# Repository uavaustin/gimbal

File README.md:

# gimbal
Hardware and software for UAV Austin's homebrew gimbal.

Notes:
 - MPU two jst connectors align with 7 pin header connected to STM
   - SPI connections
 - Voltage Rgulator rated for 12-13V input. Outputs 3.3V up to 250 mA
 - CP2102 USB to UART converter
 - Boot0 and Boot1 in 3 and 4 pin arrangement for programming settings
   - Boot0 connects to either ground or PWR (3.3V)
   - Boot1  (PB2) connects to ground, PWR, or the motor controller
 - MPU goes on its own board seperate from the STM, DRV, CP2102, USB, and Voltage Regulator
 - Jumper to connect NRST to ground or external input voltage
 - PA13/14 jtag | PB4/5/6/7 SPI on STM
 - 2 sets of 2 header pins to get power from battery

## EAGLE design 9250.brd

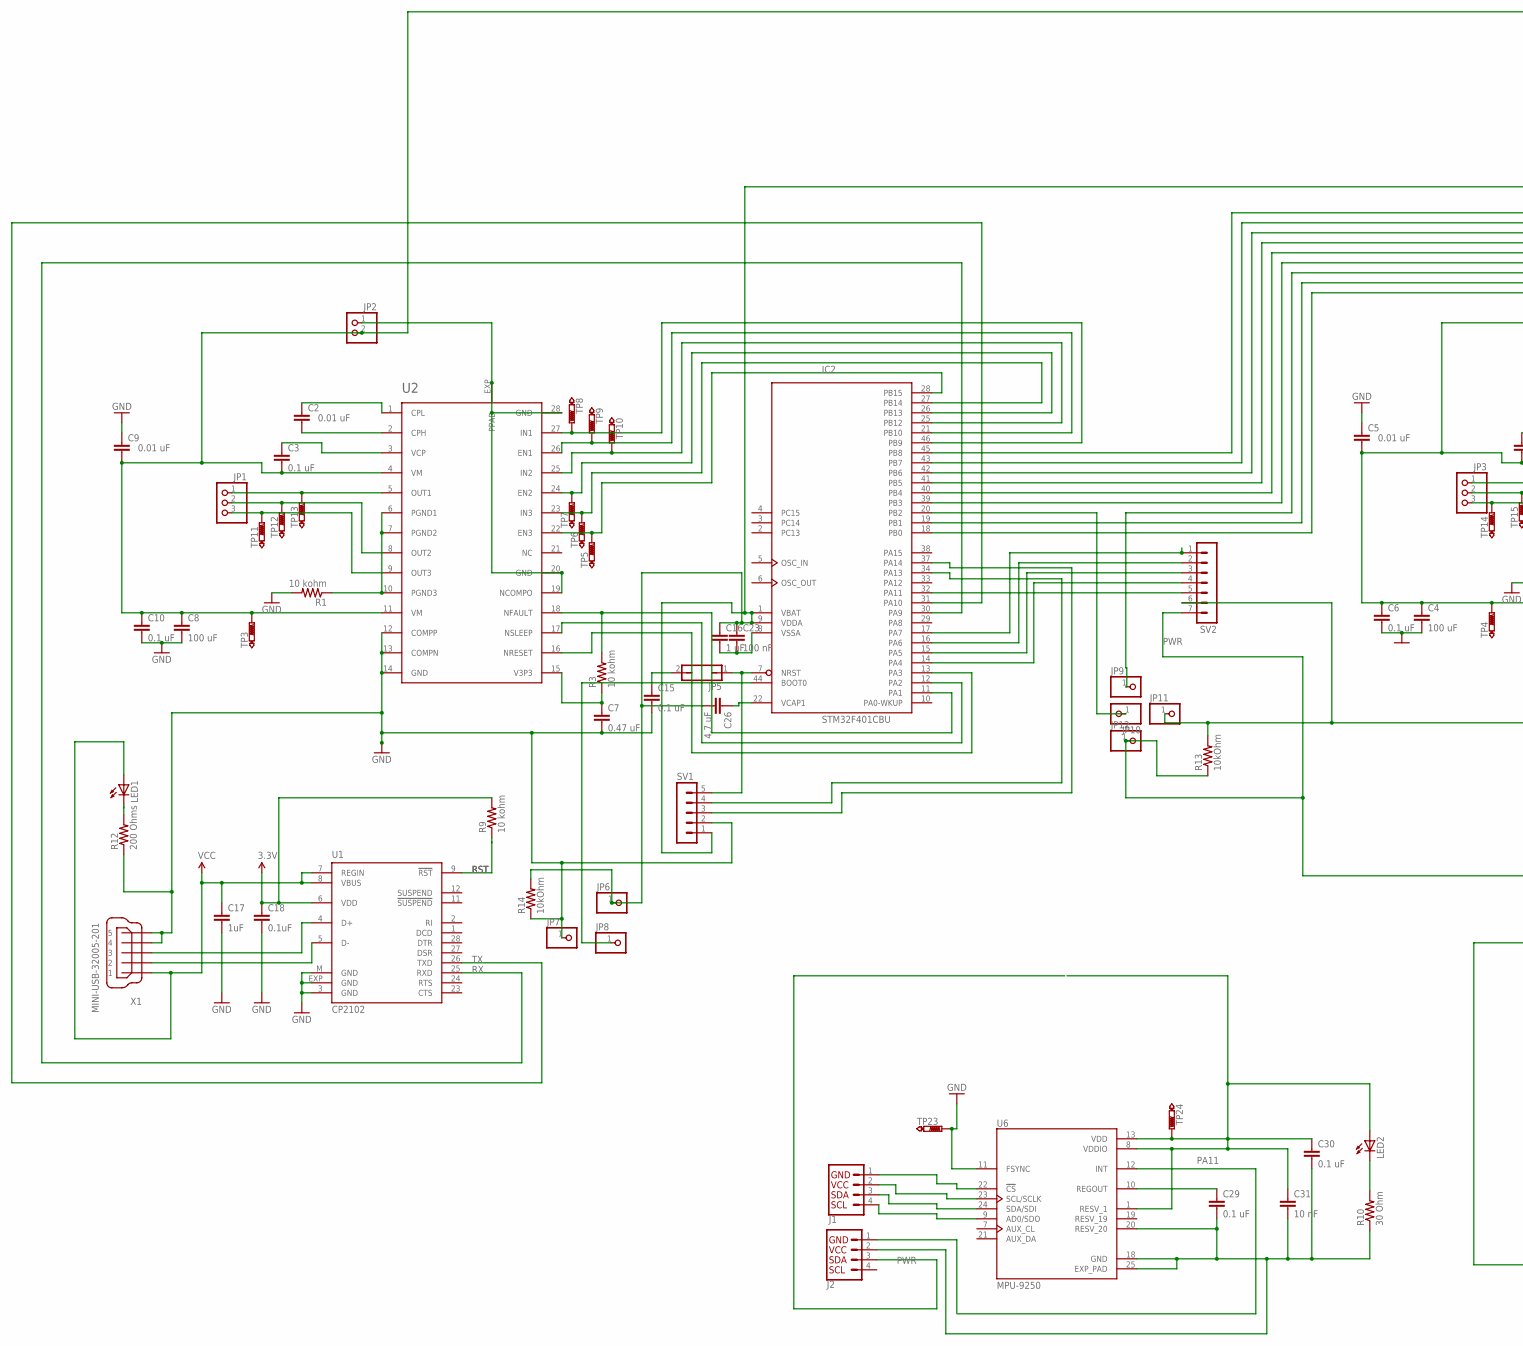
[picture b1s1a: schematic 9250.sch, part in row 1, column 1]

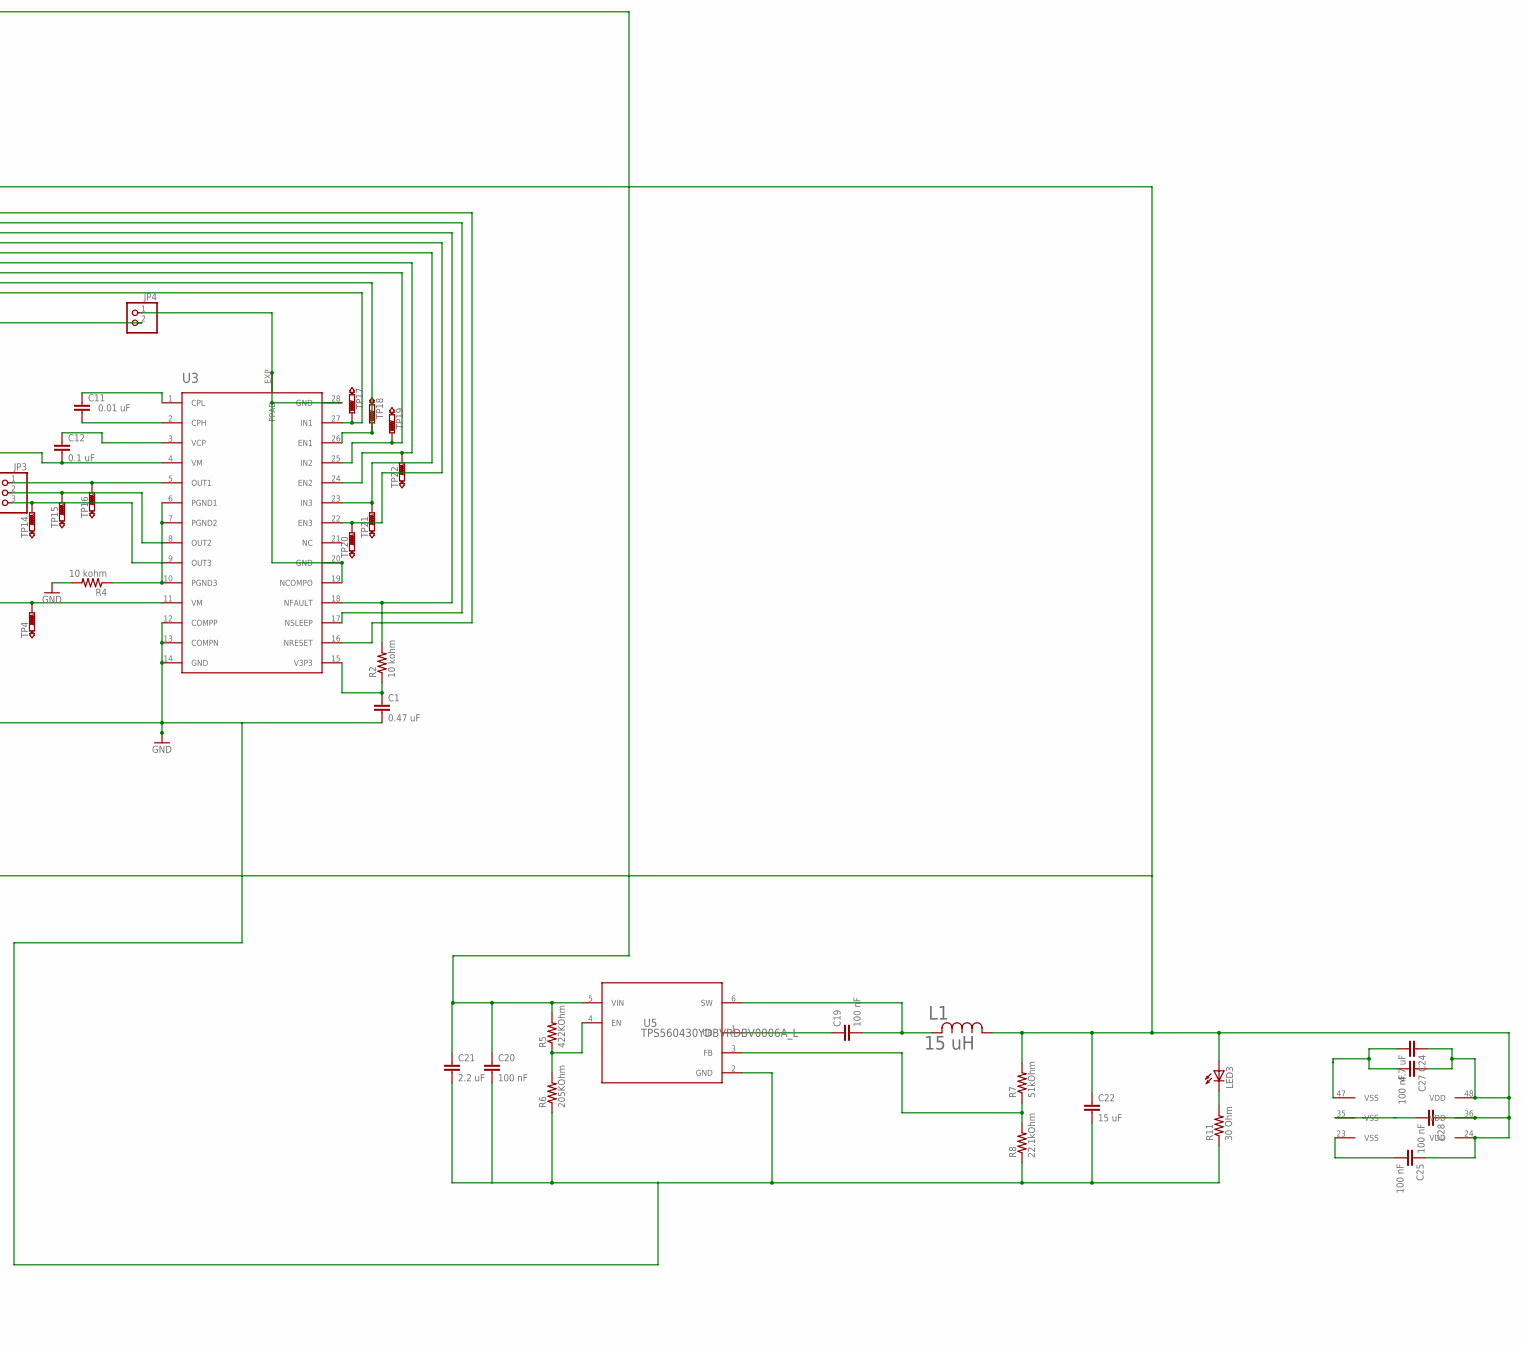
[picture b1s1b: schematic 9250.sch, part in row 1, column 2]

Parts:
C1, C7: 0.47 uF; C1210K
C2, C5, C9, C11: 0.01 uF; C1210K
C3, C6, C10, C12, C15: 0.1 uF; C1210K
C4, C8: 100 uF; C1210K
C16: 1 uF; C1210K
C17: 1uF; 0603
C18: 0.1uF; 0603
C19, C20: 100 nF; C0402K
C21: 2.2 uF; C0402K
C22: 15 uF; C0402K
C23, C25, C27, C28: 100 nF; C1210K
C24, C26: 4.7 uF; C1210K
C29, C30: 0.1 uF; C025-025X050
C31: 10 nF; C025-025X050
IC2: STM32F401CBU; UFQFPN48
J1, J2: QWIIC_CONNECTORJS-1MM; 1X04_1MM_RA
JP1, JP3: PINHD-1X3/90; 1X03/90
JP2, JP4: PINHD-1X2/90; 1X02/90
JP5: JP1Q; JP1
JP6, JP7, JP8, JP9, JP10, JP11, JP12: PINHD-1X1; 1X01
L1: 15 uH; IND_BOURNS_SRN3015
LED1, LED2, LED3: LED_ESML0603; LED_SML0603
R1, R2, R3, R4, R9: 10 kohm; M2012
R5: 422KOhm; M0805
R6: 205KOhm; M0805
R7: 51kOhm; M0805
R8: 22.1kOhm; M0805
R10, R11: 30 Ohm; M0805
R12: 200 Ohms; M0805
R13, R14: 10kOhm; M0805
SV1: MA05-1
SV2: MA07-1
TP3, TP4, TP5, TP6, TP7, TP8, TP9, TP10, TP11, TP12, TP13, TP14, TP15, TP16, TP17, TP18, TP19, TP20, TP21, TP22, TP23, TP24: PTR1TP12R; TP12R
U1: CP2102; MLP28
U2, U3: DRV8313PWPR; HTSSOP28PWP
U5: TPS560430YDBVRDBV0006A_L; DBV0006A_L
U6: MPU-9250; QFN40P300X300X105-25N
X1: MINI-USB-32005-201; 32005-201

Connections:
3.3V: C18.1, R9.2, U1.6 (VDD)
BATTERY: C3.2, C8.1, C9.2, C10.1, C20.1, C21.1, JP2.2, R5.2, TP3.TP, U2.4 (VM), U2.11 (VM), U5.5 (VIN)
BATTERY1: C4.1, C5.2, C6.1, C12.2, JP4.2, TP4.TP, U3.4 (VM), U3.11 (VM)
CPH: C2.2, U2.2 (CPH)
CPH1: C11.2, U3.2 (CPH)
CPL: C2.1, U2.1 (CPL)
CPL1: C11.1, U3.1 (CPL)
EN4: IC2.19 (PB1), TP18.TP, U3.26 (EN1)
EN5: IC2.39 (PB3), TP22.TP, U3.24 (EN2)
EN6: IC2.41 (PB5), TP20.TP, U3.22 (EN3)
GND: C1.2, C4.2, C5.1, C6.2, C7.2, C8.2, C9.1, C10.2, C15.2, C17.2, C18.2, JP2.1, JP4.1, JP7.1, JP11.1, R1.2, R4.2, R12.1, R13.2, R14.1, SV1.2, SV2.6, TP23.TP, U1.3 (GND), U1.EXP (GND), U1.M (GND), U2.12 (COMPP), U2.13 (COMPN), U2.14 (GND), U2.19 (NCOMPO), U2.20 (GND), U2.28 (GND), U2.EXP (PPAD), U3.12 (COMPP), U3.13 (COMPN), U3.14 (GND), U3.19 (NCOMPO), U3.20 (GND), U3.28 (GND), U3.EXP (PPAD), U6.11 (FSYNC), X1.4, X1.5
IN4: IC2.18 (PB0), TP17.TP, U3.27 (IN1)
IN5: JP9.1, TP19.TP, U3.25 (IN2)
IN6: IC2.40 (PB4), TP21.TP, U3.23 (IN3)
unnamed: IC2.32 (PA11), SV2.5
unnamed: IC2.46 (PB9), TP8.TP, U2.27 (IN1)
unnamed: IC2.21 (PB10), TP9.TP, U2.26 (EN1)
unnamed: C15.1, JP5.2
unnamed: C29.1, U6.10 (REGOUT)
unnamed: IC2.30 (PA9), U1.25 (RXD)
unnamed: IC2.31 (PA10), U1.26 (TXD)
unnamed: IC2.17 (PA7), SV2.1
unnamed: C26.1, IC2.22 (VCAP1)
unnamed: IC2.14 (PA4), SV2.4
unnamed: IC2.25 (PB12), TP10.TP, U2.25 (IN2)
unnamed: C30.1, C31.1, LED2.A, TP24.TP, U6.1 (RESV_1), U6.8 (VDDIO), U6.13 (VDD)
unnamed: IC2.26 (PB13), TP7.TP, U2.24 (EN2)
unnamed: IC2.27 (PB14), TP6.TP, U2.23 (IN3)
unnamed: IC2.28 (PB15), TP5.TP, U2.22 (EN3)
unnamed: IC2.7 (NRST), JP5.1, SV1.5
unnamed: C20.2, C21.2, C22.2, R6.1, R8.1, R11.1, U5.2 (GND)
unnamed: U1.5 (D-), X1.2
unnamed: U1.4 (D+), X1.3
unnamed: IC2.44 (BOOT0), JP8.1
unnamed: C24.2, C27.2, IC2.47 (VSS)
unnamed: LED2.C, R10.2
unnamed: R5.1, R6.2, U5.4 (EN)
unnamed: C19.1, U5.1 (CB)
unnamed: C19.2, L1.2, U5.6 (SW)
unnamed: C25.2, IC2.23 (VSS)
unnamed: R7.1, R8.2, U5.3 (FB)
unnamed: C28.2, IC2.35 (VSS)
unnamed: C16.2, C23.2, IC2.8 (VSSA)
unnamed: C29.2, C30.2, C31.2, J2.2, R10.1, U6.18 (GND), U6.20 (RESV_20), U6.25 (EXP_PAD)
unnamed: LED3.C, R11.2
unnamed: LED1.C, R12.2
unnamed: IC2.15 (PA5), SV2.3
unnamed: IC2.16 (PA6), SV2.2
unnamed: IC2.20 (PB2), JP10.1
NFAULT: IC2.11 (PA1), R3.2, U2.18 (NFAULT)
NFAULT1: IC2.42 (PB6), R2.2, U3.18 (NFAULT)
NRESET: IC2.13 (PA3), U2.16 (NRESET)
NRESET1: IC2.45 (PB8), U3.16 (NRESET)
NSLEEP: IC2.12 (PA2), U2.17 (NSLEEP)
NSLEEP1: IC2.43 (PB7), U3.17 (NSLEEP)
OUT1: JP1.1, TP13.TP, U2.5 (OUT1)
OUT2: JP1.2, TP12.TP, U2.8 (OUT2)
OUT3: JP1.3, TP11.TP, U2.9 (OUT3)
OUT4: JP3.1, TP16.TP, U3.5 (OUT1)
OUT5: JP3.2, TP15.TP, U3.8 (OUT2)
OUT6: JP3.3, TP14.TP, U3.9 (OUT3)
PA11: U6.12 (INT)
PA12: J1.4, U6.9 (AD0/SDO)
PA13: J1.3, U6.24 (SDA/SDI)
PA14: J1.2, U6.23 (SCL/SCLK)
PA15: J1.1, U6.22 (!CS)
PGND: R1.1, U2.6 (PGND1), U2.7 (PGND2), U2.10 (PGND3)
PGND1: R4.1, U3.6 (PGND1), U3.7 (PGND2), U3.10 (PGND3)
PWR: C16.1, C22.1, C23.1, C24.1, C25.1, C26.2, C27.1, C28.1, IC2.1 (VBAT), IC2.9 (VDDA), IC2.24 (VDD), IC2.36 (VDD), IC2.48 (VDD), J2.3, JP6.1, JP12.1, L1.1, LED3.A, R7.2, R13.1, R14.2, SV1.1, SV2.7
RST: R9.1, U1.9 (!RST)
RX: IC2.34 (PA13), SV1.4
TX: IC2.37 (PA14), SV1.3
V3P1: C1.1, R2.1, U3.15 (V3P3)
V3P3: C7.1, R3.1, U2.15 (V3P3)
VCC: C17.1, LED1.A, U1.7 (REGIN), U1.8 (VBUS), X1.1
VCP: C3.1, U2.3 (VCP)
VCP1: C12.1, U3.3 (VCP)

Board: 2 copper layers, 92 parts (0 on the bottom side), 76 nets, no tracks yet.

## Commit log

2019-04-14 Schematic

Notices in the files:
parts and their libraries:
SparkFun-Connectors: Licensing: Creative Commons ShareAlike 4.0 International - https://creativecommons.org/licenses/by-sa/4.0
